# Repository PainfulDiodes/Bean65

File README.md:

# Bean65

6502 homebrew computer that can take advantage of [BeanBoard](https://github.com/PainfulDiodes/BeanBoard) and [BeanBoardSPI](https://github.com/PainfulDiodes/BeanBoardSPI) peripherals which were originally designed for the Z80 [BeanZee](https://github.com/PainfulDiodes/BeanZee).

See also: [PainfulDiodes Blog: Bean65](https://painfuldiodes.wordpress.com/category/bean65/)

- W65C02S CPU
- 2MHz clock
- 32k ROM
- 16k RAM
- W65C22N VIA

## CPU Bus

The CPU bus touches only ROM, RAM and the VIA, decoded with a single 74HCT00 based on Garth Wilson's [simple ROM/RAM/VIA design](https://wilsonminesco.com/6502primer/potpourri.html): RAM at 0000-3FFF, the VIA at 4000-7FFF and ROM at 8000-FFFF.

Using a reset supervisor frees up one NAND, and dedicating the IO address range to a single VIA frees up a second.

One of these is used to invert R/W# for the ROM's OE#, so the ROM only drives the bus on reads and a stray write to a ROM address can't cause bus contention.

The other provides BeanBoard's RD# (see below).

## Slow Bus / BeanBoard Interface

Every peripheral sits on a "slow bus" behind the VIA, under software control, allowing for slower devices to be connected (and 6502 dummy reads can't reach them).

The slow bus provides 6502-style signals - address and R/W#, with the addition of an I/O enable strobe.

These are made available through two 2x7 VIA Interface headers (in [Garth Wilson's VIA connector format](https://wilsonminesco.com/6502primer/potpourri.html#BAS_CPU)).

These also map economically onto BeanBoard's Z80-style bus: the strobe provides IORQ#, R/W# serves directly as WR#, and the other freed 74HCT00 gate inverts R/W# for RD#. Bean65 plugs into the BeanBoard's sockets.

## BeanPort

The [BeanPort](https://github.com/PainfulDiodes/BeanPort) USB interface was designed so it can plug directly into Bean65's VIA connectors.

## Multi-mode

Bean65 was designed to cooperate with the existing BeanBoard and BeanBoardSPI peripherals. This required some compromises: the BeanBoard interface and connectors suit the Z80 bus, so the slow bus is adapted to fit them. Designed from scratch, the VIA slow bus would be used throughout.

When neither BeanPort nor BeanBoard is connected, with the Bean65 in standalone mode, the VIA connectors are available for general-purpose use.

If BeanPort is connected, the slow bus IO enable strobe is routed to BeanPort via a jumper - making it the only IO device attached to the Bean65.

When both BeanPort and BeanBoard are connected, the jumper is removed and BeanBoard, which decodes A1-A3, returns BeanPort's enable through the jumper header (as on BeanZee), so that both BeanPort and BeanBoard share the slow bus. In this configuration the Bean65 has USB, keyboard and a small LCD display available.

BeanBoardSPI can piggyback on BeanBoard and provide storage and replace the character LCD with a TFT display.

## Schematic

[kicad/bean65.pdf](kicad/bean65.pdf)

## Breadboard Prototype

A prototype (without RAM or VIA) has an Arduino Mega generating the clock and monitoring the bus, an 8k AT28C64B ROM, and BeanPort directly on the CPU bus:

[kicad_breadboard/bean65.pdf](kicad_breadboard/bean65.pdf)

## Links

- [Garth Wilson's 6502 primer](https://wilsonminesco.com/6502primer/)
- [BeanZee](https://github.com/PainfulDiodes/BeanZee)
- [BeanBoard](https://github.com/PainfulDiodes/BeanBoard)
- [BeanBoardSPI](https://github.com/PainfulDiodes/BeanBoardSPI)
- [BeanPort](https://github.com/PainfulDiodes/BeanPort)

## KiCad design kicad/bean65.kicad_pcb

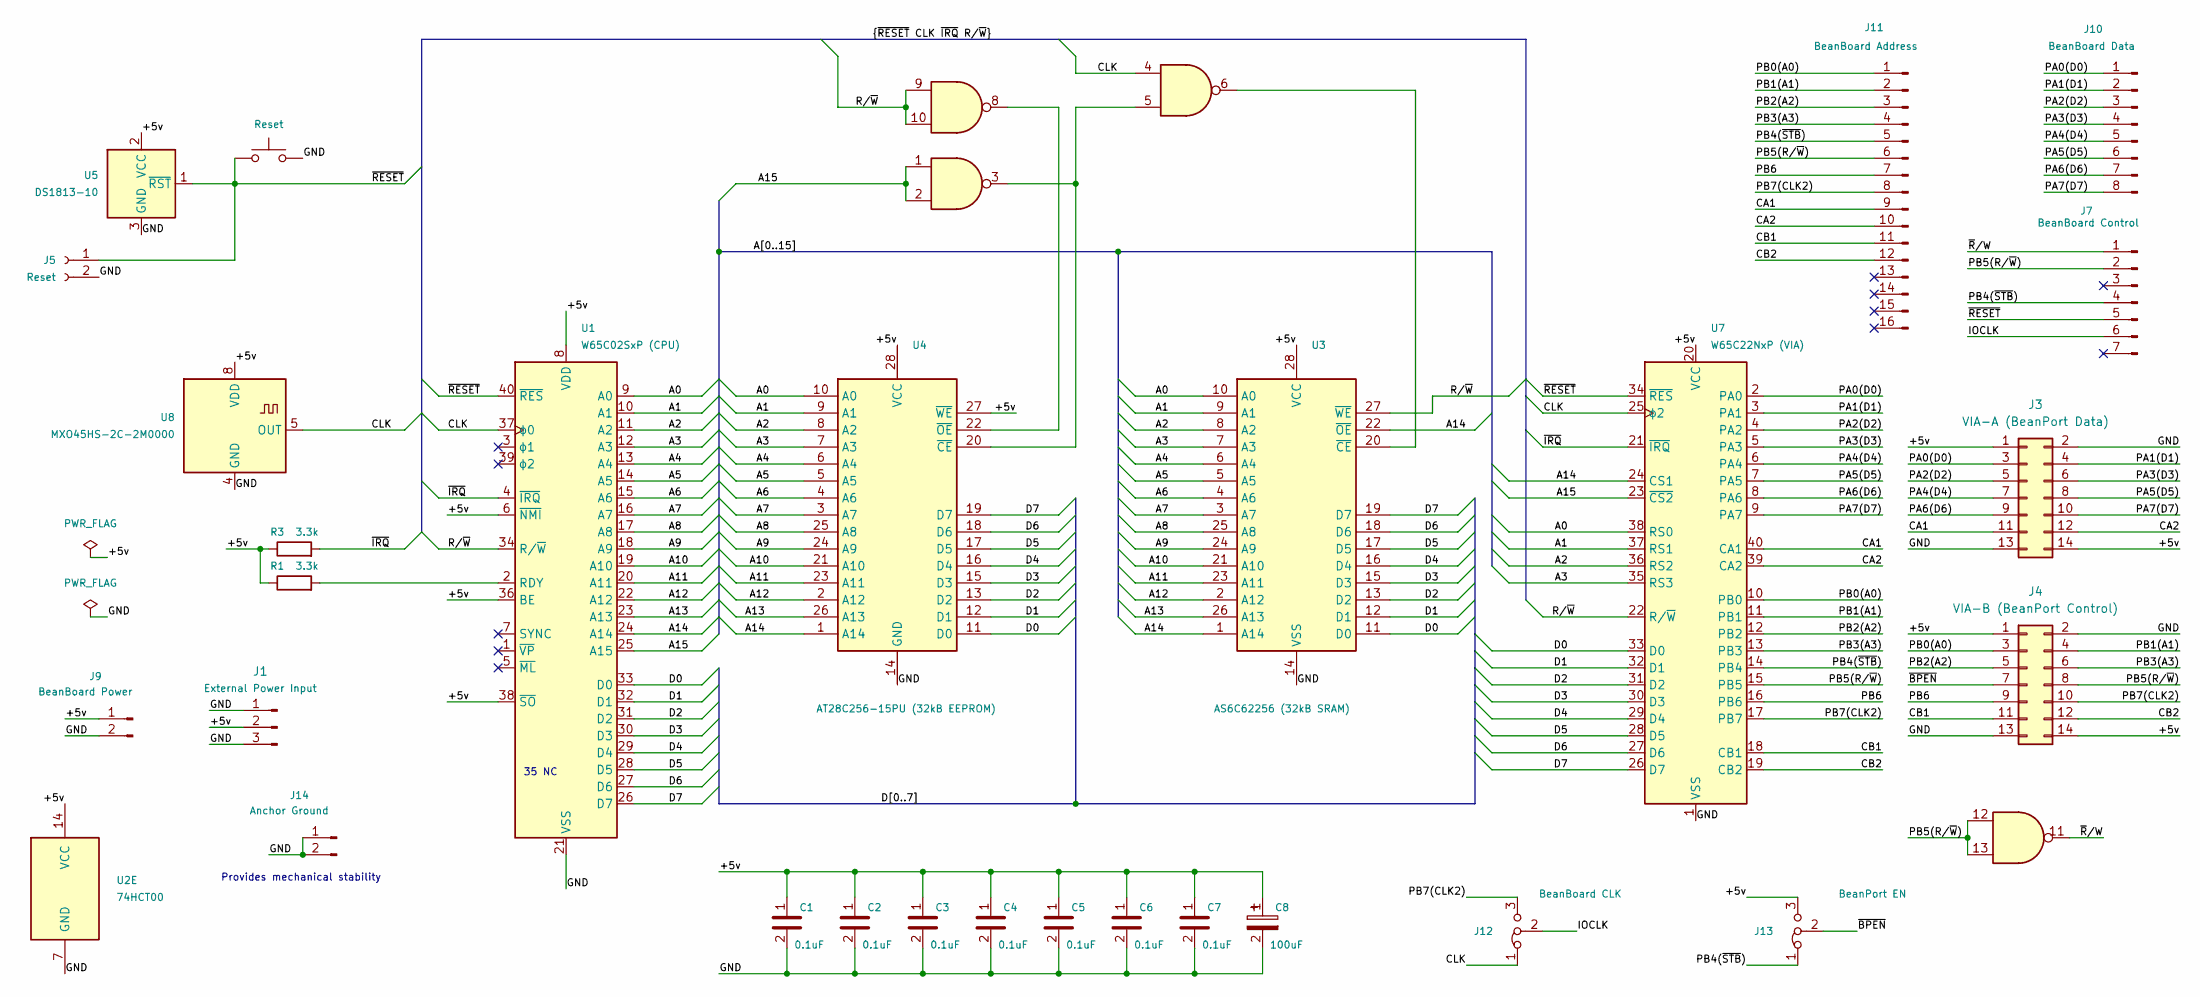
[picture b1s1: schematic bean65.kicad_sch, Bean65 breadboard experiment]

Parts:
C1, C2, C3, C4, C5, C6, C7: 0.1uF; C_Disc_D5.0mm_W2.5mm_P2.50mm
C8: 100uF; CP_Radial_D5.0mm_P2.00mm
J1: External Power Input; PinHeader_1x03_P2.54mm_Vertical
J3: VIA-A (BeanPort Data); PinHeader_2x07_P2.54mm_Vertical_IDC_Clearance
J4: VIA-B (BeanPort Control); PinHeader_2x07_P2.54mm_Vertical_IDC_Clearance
J5: Reset; PinSocket_1x02_P2.54mm_Vertical
J7: BeanBoard Control; PinHeader_1x07_P2.54mm_Vertical
J9: BeanBoard Power; PinHeader_1x02_P2.54mm_Vertical
J10: BeanBoard Data; PinHeader_1x08_P2.54mm_Vertical
J11: BeanBoard Address; PinHeader_1x16_P2.54mm_Vertical
J12: BeanBoard CLK; PinHeader_1x03_P2.54mm_Vertical
J13: BeanPort EN; PinHeader_1x03_P2.54mm_Vertical
J14: Anchor Ground; PinHeader_1x02_P2.54mm_Vertical
R1, R3: 3.3k; R_Axial_DIN0204_L3.6mm_D1.6mm_P7.62mm_Horizontal
SW1: Reset; SW_PUSH_6mm_H5mm
U1: W65C02SxP (CPU); DIP-40_W15.24mm
U2: 74HCT00; DIP-14_W7.62mm
U3: AS6C62256 (32kB SRAM); DIP-28_W15.24mm; Mouser Part Number 913-AS6C62256-55PCN
U4: AT28C256-15PU (32kB EEPROM); DIP-28_W15.24mm; Manufacturer_Part_Number AT28C256-15PU
U5: DS1813-10; TO-92_Inline
U7: W65C22NxP (VIA); DIP-40_W15.24mm
U8: MXO45HS-2C-2M0000; Oscillator_DIP-8

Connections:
/+5v: C1.1, C2.1, C3.1, C4.1, C5.1, C6.1, C7.1, C8.1, J1.2, J3.1, J3.14, J4.1, J4.14, J9.1, J13.3 (B), R1.1, R3.1, U1.6 (~NMI), U1.8 (VDD), U1.36 (BE), U1.38 (~SO), U2.14 (VCC), U3.28 (VCC), U4.27 (~WE), U4.28 (VCC), U5.2 (VCC), U7.20 (VCC), U8.8 (VDD)
/A0: U1.9 (A0), U3.10 (A0), U4.10 (A0), U7.38 (RS0)
/A1: U1.10 (A1), U3.9 (A1), U4.9 (A1), U7.37 (RS1)
/A2: U1.11 (A2), U3.8 (A2), U4.8 (A2), U7.36 (RS2)
/A3: U1.12 (A3), U3.7 (A3), U4.7 (A3), U7.35 (RS3)
/A4: U1.13 (A4), U3.6 (A4), U4.6 (A4)
/A5: U1.14 (A5), U3.5 (A5), U4.5 (A5)
/A6: U1.15 (A6), U3.4 (A6), U4.4 (A6)
/A7: U1.16 (A7), U3.3 (A7), U4.3 (A7)
/A8: U1.17 (A8), U3.25 (A8), U4.25 (A8)
/A9: U1.18 (A9), U3.24 (A9), U4.24 (A9)
/A10: U1.19 (A10), U3.21 (A10), U4.21 (A10)
/A11: U1.20 (A11), U3.23 (A11), U4.23 (A11)
/A12: U1.22 (A12), U3.2 (A12), U4.2 (A12)
/A13: U1.23 (A13), U3.26 (A13), U4.26 (A13)
/A14: U1.24 (A14), U3.1 (A14), U3.22 (~OE), U4.1 (A14), U7.24 (CS1)
/A15: U1.25 (A15), U2.1, U2.2, U7.23 (~CS2)
/CA1: J3.11, J11.9, U7.40 (CA1)
/CA2: J3.12, J11.10, U7.39 (CA2)
/CB1: J4.11, J11.11, U7.18 (CB1)
/CB2: J4.12, J11.12, U7.19 (CB2)
/CLK: J12.1 (A), U1.37 (ϕ0), U2.4, U7.25 (ϕ2), U8.5 (OUT)
/D0: U1.33 (D0), U3.11 (D0), U4.11 (D0), U7.33 (D0)
/D1: U1.32 (D1), U3.12 (D1), U4.12 (D1), U7.32 (D1)
/D2: U1.31 (D2), U3.13 (D2), U4.13 (D2), U7.31 (D2)
/D3: U1.30 (D3), U3.15 (D3), U4.15 (D3), U7.30 (D3)
/D4: U1.29 (D4), U3.16 (D4), U4.16 (D4), U7.29 (D4)
/D5: U1.28 (D5), U3.17 (D5), U4.17 (D5), U7.28 (D5)
/D6: U1.27 (D6), U3.18 (D6), U4.18 (D6), U7.27 (D6)
/D7: U1.26 (D7), U3.19 (D7), U4.19 (D7), U7.26 (D7)
/GND: C1.2, C2.2, C3.2, C4.2, C5.2, C6.2, C7.2, C8.2, J1.1, J1.3, J3.2, J3.13, J4.2, J4.13, J5.2, J9.2, J14.1, J14.2, SW1.2, U1.21 (VSS), U2.7 (GND), U3.14 (VSS), U4.14 (GND), U5.3 (GND), U7.1 (VSS), U8.4 (GND)
/IOCLK: J7.6, J12.2 (C)
/PA0(D0): J3.3, J10.1, U7.2 (PA0)
/PA1(D1): J3.4, J10.2, U7.3 (PA1)
/PA2(D2): J3.5, J10.3, U7.4 (PA2)
/PA3(D3): J3.6, J10.4, U7.5 (PA3)
/PA4(D4): J3.7, J10.5, U7.6 (PA4)
/PA5(D5): J3.8, J10.6, U7.7 (PA5)
/PA6(D6): J3.9, J10.7, U7.8 (PA6)
/PA7(D7): J3.10, J10.8, U7.9 (PA7)
/PB0(A0): J4.3, J11.1, U7.10 (PB0)
/PB1(A1): J4.4, J11.2, U7.11 (PB1)
/PB2(A2): J4.5, J11.3, U7.12 (PB2)
/PB3(A3): J4.6, J11.4, U7.13 (PB3)
/PB4(~STB): J7.4, J11.5, J13.1 (A), U7.14 (PB4)
/PB5(R/~W): J4.8, J7.2, J11.6, U2.12, U2.13, U7.15 (PB5)
/PB6: J4.9, J11.7, U7.16 (PB6)
/PB7(CLK2): J4.10, J11.8, J12.3 (B), U7.17 (PB7)
/R/~W: U1.34 (R/~W), U2.9, U2.10, U3.27 (~WE), U7.22 (R/~W)
/~BPEN: J4.7, J13.2 (C)
/~IRQ: R3.2, U1.4 (~IRQ), U7.21 (~IRQ)
/~RESET: J5.1, J7.5, SW1.1, U1.40 (~RES), U5.1 (~RST), U7.34 (~RES)
/~R/W: J7.1, U2.11
unnamed: R1.2, U1.2 (RDY)
unnamed: U2.6, U3.20 (~CE)
unnamed: U2.3, U2.5, U4.20 (~CE)
unnamed: U2.8, U4.22 (~OE)

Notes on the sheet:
Provides mechanical stability
35 NC

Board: 2 copper layers, 30 parts (5 on the bottom side), 57 nets, no tracks yet.

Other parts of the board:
GUIDE**: BeanBoard_Guide
